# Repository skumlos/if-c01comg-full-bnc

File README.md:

IF-C01COMG Full BNC Clone board SMD

This is a full sized version of the IF-C01COMG board for JVC pro monitors (TM-Hxx50CG) and some others...

It is created as a very close to 1:1 copy of the original (sans the stereo-to-mono mixing circuit and internal 75R term option)
thus it has dual stack BNCs, which are pretty expensive, to allow for passthrough of video signals.

Board is for now completely untested...

You're welcome to clone, sell, re-design and whatever, see LICENSE.

(2022) Martin Hejnfelt (martin@hejnfelt.com)
This work is free. You can redistribute it and/or modify it under the
terms of the Do What The Fuck You Want To Public License, Version 2,
as published by Sam Hocevar. See the LICENSE file for more details.

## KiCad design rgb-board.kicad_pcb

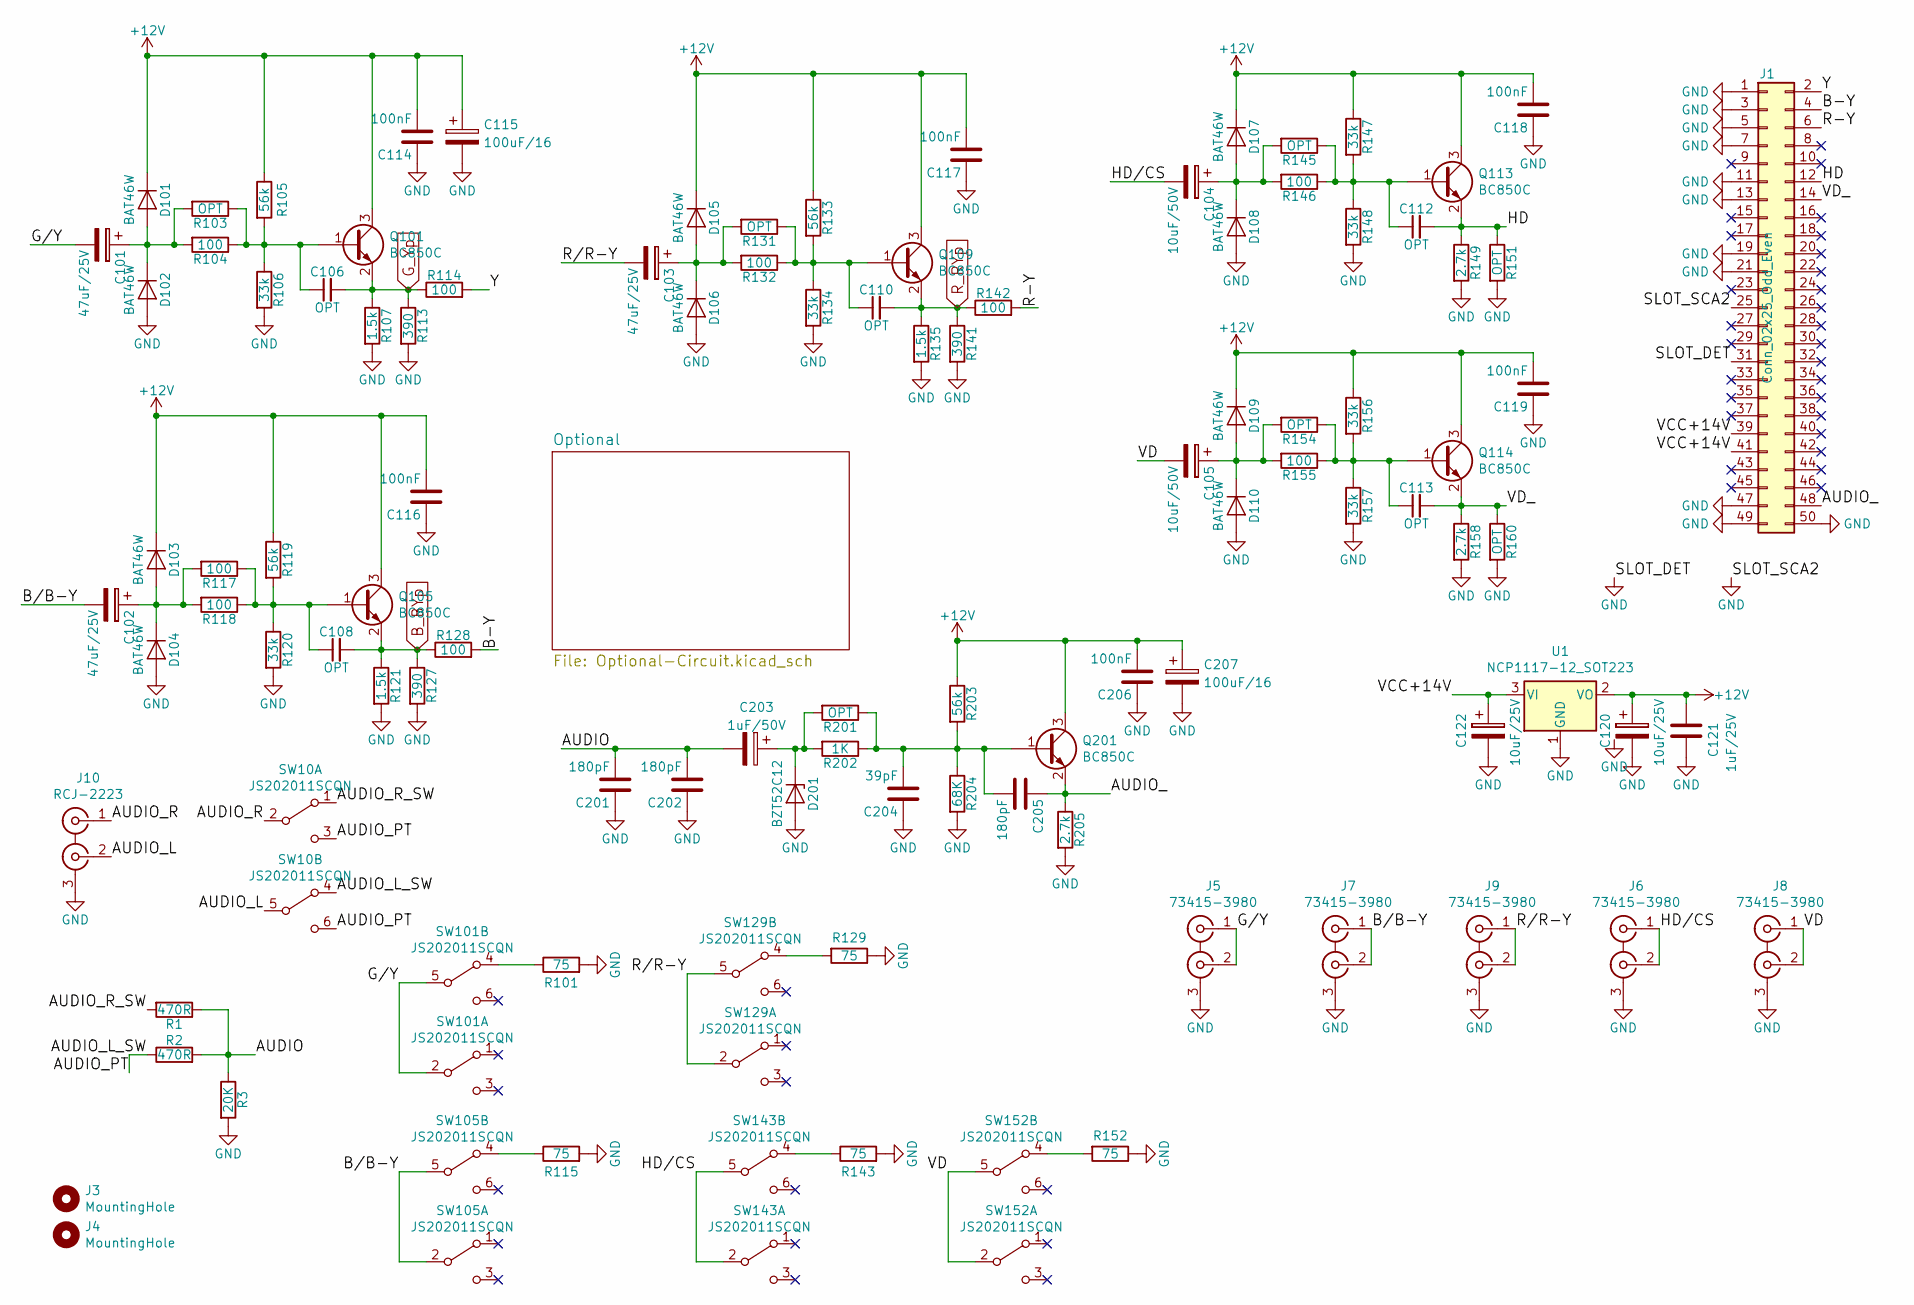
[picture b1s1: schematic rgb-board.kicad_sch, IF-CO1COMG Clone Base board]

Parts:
C101, C102, C103: 47uF/25V; C_Elec_6.3x5.4; JLC SMD,6.3x6.1mm
C104, C105: 10uF/50V; C_Elec_5x5.4; JLC SMD,5x5.4mm
C106, C108, C110, C112, C113: OPT; C_0805_2012Metric_Pad1.18x1.45mm_HandSolder
C114, C116, C117, C118, C119, C206: 100nF; C_0805_2012Metric_Pad1.18x1.45mm_HandSolder; JLC 0805
C115, C207: 100uF/16; CP_Elec_6.3x5.4; JLC SMD,6.3x5.4mm
C120, C122: 10uF/25V; C_Elec_5x5.4; JLC SMD,5x5.4mm
C121: 1uF/25V; C_0805_2012Metric_Pad1.18x1.45mm_HandSolder; JLC 0805
C201, C202, C205: 180pF; C_0805_2012Metric_Pad1.18x1.45mm_HandSolder; JLC 0805
C203: 1uF/50V; CP_Elec_4x5.4; JLC SMD,4x5.4mm
C204: 39pF; C_0805_2012Metric_Pad1.18x1.45mm_HandSolder; JLC 0805
D101, D102, D103, D104, D105, D106, D107, D108, D109, D110: BAT46W; D_SOD-123; JLC SOD-123
D201: BZT52C12; D_SOD-123; JLC SOD-123
J1: Conn_02x25_Odd_Even; Pin_Header_Angled_2x25_Pitch2.54mm
J3, J4: MountingHole; MountingHole_3.2mm_M3
J5, J6, J7, J8, J9: 73415-3980
J10: RCJ-2223; RCJ-22XX
Q101, Q105, Q109, Q113, Q114, Q201: BC850C; SOT-23_Handsoldering; JLC SOT-23(SOT-23-3)
R1, R2: 470R; R_0805_2012Metric_Pad1.20x1.40mm_HandSolder; JLC 0805
R3: 20K; R_0805_2012Metric_Pad1.20x1.40mm_HandSolder; JLC 0805
R101, R115, R129, R143, R152: 75; R_0805_2012Metric_Pad1.20x1.40mm_HandSolder; JLC 0805
R103, R131, R145, R151, R154, R160, R201: OPT; R_0805_2012Metric_Pad1.20x1.40mm_HandSolder; JLC 0805
R104, R114, R117, R118, R128, R132, R142, R146, R155: 100; R_0805_2012Metric_Pad1.20x1.40mm_HandSolder; JLC 0805
R105, R119, R133, R203: 56k; R_0805_2012Metric_Pad1.20x1.40mm_HandSolder; JLC 0805
R106, R120, R134, R147, R148, R156, R157: 33k; R_0805_2012Metric_Pad1.20x1.40mm_HandSolder; JLC 0805
R107, R121, R135: 1.5k; R_0805_2012Metric_Pad1.20x1.40mm_HandSolder; JLC 0805
R113, R127, R141: 390; R_0805_2012Metric_Pad1.20x1.40mm_HandSolder; JLC 0805
R149, R158, R205: 2.7k; R_0805_2012Metric_Pad1.20x1.40mm_HandSolder; JLC 0805
R202: 1K; R_0805_2012Metric_Pad1.20x1.40mm_HandSolder; JLC 0805
R204: 68K; R_0805_2012Metric_Pad1.20x1.40mm_HandSolder; JLC 0805
SW10, SW101, SW105, SW129, SW143, SW152: JS202011SCQN; JLC SMD
U1: NCP1117-12_SOT223; SOT-223-3_TabPin2

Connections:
+12V: C114.2, C115.1, C116.2, C117.2, C118.2, C119.2, C120.1, C121.2, C206.2, C207.1, D101.1 (K), D103.1 (K), D105.1 (K), D107.1 (K), D109.1 (K), Q101.3 (C), Q105.3 (C), Q109.3 (C), Q113.3 (C), Q114.3 (C), Q201.3 (C), R105.1, R119.1, R133.1, R147.1, R156.1, R203.1, U1.2 (VO); also elsewhere on the board
/AUDIO: C201.2, C202.2, C203.2, R1.1, R2.2, R3.1
/AUDIO_: C205.1, J1.48, Q201.2 (E), R205.1
/AUDIO_L: J10.2 (IN2), SW10.5 (B)
/AUDIO_L_SW: R2.1, SW10.3 (C), SW10.4 (A), SW10.6 (C)
/AUDIO_R: J10.1 (IN1), SW10.2 (B)
/AUDIO_R_SW: R1.2, SW10.1 (A)
/B-Y: J1.4, R128.2
/B/B-Y: C102.2, J7.1 (IN1), J7.2 (IN2), SW105.2 (B), SW105.5 (B)
/G/Y: C101.2, J5.1 (IN1), J5.2 (IN2), SW101.2 (B), SW101.5 (B)
/HD: C112.2, J1.12, Q113.2 (E), R149.1, R151.1
/HD/CS: C104.2, J6.1 (IN1), J6.2 (IN2), SW143.2 (B), SW143.5 (B)
/R-Y: J1.6, R142.2
/R/R-Y: C103.2, J9.1 (IN1), J9.2 (IN2), SW129.2 (B), SW129.5 (B)
/VCC+14V: C122.1, J1.39, J1.41, U1.3 (VI)
/VD: C105.2, J8.1 (IN1), J8.2 (IN2), SW152.2 (B), SW152.5 (B)
/VD_: C113.2, J1.14, Q114.2 (E), R158.1, R160.1
/Y: J1.2, R114.2
B_BYp: C108.2, Q105.2 (E), R121.1, R127.1, R128.1; also elsewhere on the board
GND: C114.1, C115.2, C116.1, C117.1, C118.1, C119.1, C120.2, C121.1, C122.2, C201.1, C202.1, C204.1, C206.1, C207.2, D102.2 (A), D104.2 (A), D106.2 (A), D108.2 (A), D110.2 (A), D201.2 (A), J1.1, J1.3, J1.5, J1.7, J1.11, J1.13, J1.19, J1.21, J1.25, J1.31, J1.47, J1.49, J1.50, J5.3 (EXT), J6.3 (EXT), J7.3 (EXT), J8.3 (EXT), J9.3 (EXT), J10.3 (EXT), R3.2, R101.2, R106.2, R107.2, R113.2, R115.2, R120.2, R121.2, R127.2, R129.1, R134.2, R135.2, R141.2, R143.2, R148.2, R149.2, R151.2, R152.1, R157.2, R158.2, R160.2, R204.2, R205.2, U1.1 (GND); also elsewhere on the board
G_Yp: C106.2, Q101.2 (E), R107.1, R113.1, R114.1; also elsewhere on the board
unnamed: C101.1, D101.2 (A), D102.1 (K), R103.2, R104.2
unnamed: C102.1, D103.2 (A), D104.1 (K), R117.2, R118.2
unnamed: C103.1, D105.2 (A), D106.1 (K), R131.2, R132.2
unnamed: C104.1, D107.2 (A), D108.1 (K), R145.2, R146.2
unnamed: C105.1, D109.2 (A), D110.1 (K), R154.2, R155.2
unnamed: C106.1, Q101.1 (B), R103.1, R104.1, R105.2, R106.1
unnamed: C108.1, Q105.1 (B), R117.1, R118.1, R119.2, R120.1
unnamed: C110.1, Q109.1 (B), R131.1, R132.1, R133.2, R134.1
unnamed: C112.1, Q113.1 (B), R145.1, R146.1, R147.2, R148.1
unnamed: C113.1, Q114.1 (B), R154.1, R155.1, R156.2, R157.1
unnamed: C203.1, D201.1 (K), R201.2, R202.2
unnamed: C204.2, C205.2, Q201.1 (B), R201.1, R202.1, R203.2, R204.1
unnamed: R101.1, SW101.4 (A)
unnamed: R115.1, SW105.4 (A)
unnamed: R129.2, SW129.4 (A)
unnamed: R143.1, SW143.4 (A)
unnamed: R152.2, SW152.4 (A)
R_RYp: C110.2, Q109.2 (E), R135.1, R141.1, R142.1; also elsewhere on the board

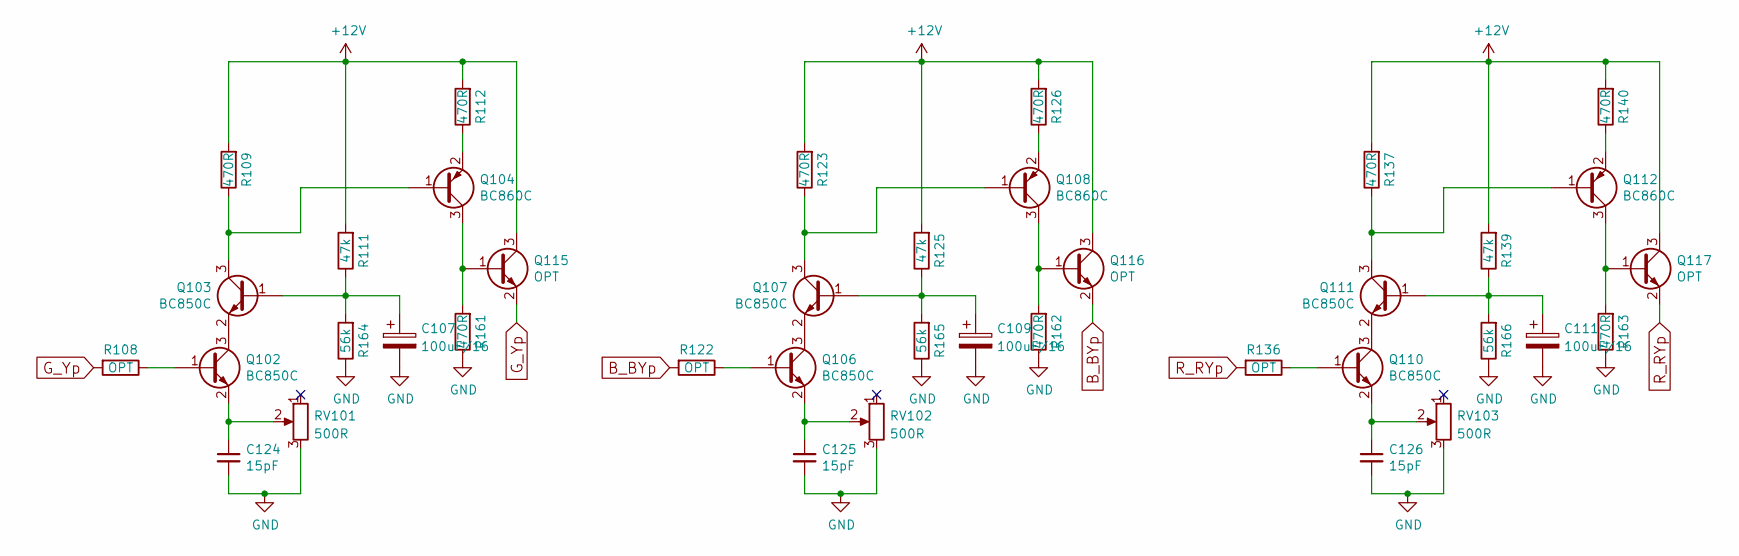
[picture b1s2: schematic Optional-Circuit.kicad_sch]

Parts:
C107, C109, C111: 100uF/16; CP_Elec_6.3x5.4; JLC SMD,6.3x5.4mm
C124, C125, C126: 15pF; C_0805_2012Metric_Pad1.18x1.45mm_HandSolder; JLC 0805
Q102, Q103, Q106, Q107, Q110, Q111: BC850C; SOT-23_Handsoldering; JLC SOT-23(SOT-23-3)
Q104, Q108, Q112: BC860C; SOT-23_Handsoldering; JLC SOT-23
Q115, Q116, Q117: OPT; SOT-23_Handsoldering
R108, R122, R136: OPT; R_0805_2012Metric_Pad1.20x1.40mm_HandSolder
R109, R112, R123, R126, R137, R140, R161, R162, R163: 470R; R_0805_2012Metric_Pad1.20x1.40mm_HandSolder; JLC 0805
R111, R125, R139: 47k; R_0805_2012Metric_Pad1.20x1.40mm_HandSolder; JLC 0805
R164, R165, R166: 56k; R_0805_2012Metric_Pad1.20x1.40mm_HandSolder; JLC 0805
RV101, RV102, RV103: 500R; Potentiometer_Bourns_3386P_Vertical

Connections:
+12V: Q115.3 (C), Q116.3 (C), Q117.3 (C), R109.2, R111.2, R112.2, R123.2, R125.2, R126.2, R137.2, R139.2, R140.2; also elsewhere on the board
B_BYp: Q116.2 (E), R122.2; also elsewhere on the board
GND: C107.2, C109.2, C111.2, C124.2, C125.2, C126.2, R161.1, R162.1, R163.1, R164.1, R165.1, R166.1, RV101.3, RV102.3, RV103.3; also elsewhere on the board
G_Yp: Q115.2 (E), R108.2; also elsewhere on the board
unnamed: C107.1, Q103.1 (B), R111.1, R164.2
unnamed: C109.1, Q107.1 (B), R125.1, R165.2
unnamed: C111.1, Q111.1 (B), R139.1, R166.2
unnamed: C124.1, Q102.2 (E), RV101.2
unnamed: C125.1, Q106.2 (E), RV102.2
unnamed: C126.1, Q110.2 (E), RV103.2
unnamed: Q102.1 (B), R108.1
unnamed: Q102.3 (C), Q103.2 (E)
unnamed: Q103.3 (C), Q104.1 (B), R109.1
unnamed: Q104.2 (E), R112.1
unnamed: Q104.3 (C), Q115.1 (B), R161.2
unnamed: Q106.1 (B), R122.1
unnamed: Q106.3 (C), Q107.2 (E)
unnamed: Q107.3 (C), Q108.1 (B), R123.1
unnamed: Q108.2 (E), R126.1
unnamed: Q108.3 (C), Q116.1 (B), R162.2
unnamed: Q110.1 (B), R136.1
unnamed: Q110.3 (C), Q111.2 (E)
unnamed: Q111.3 (C), Q112.1 (B), R137.1
unnamed: Q112.2 (E), R140.1
unnamed: Q112.3 (C), Q117.1 (B), R163.2
R_RYp: Q117.2 (E), R136.2; also elsewhere on the board

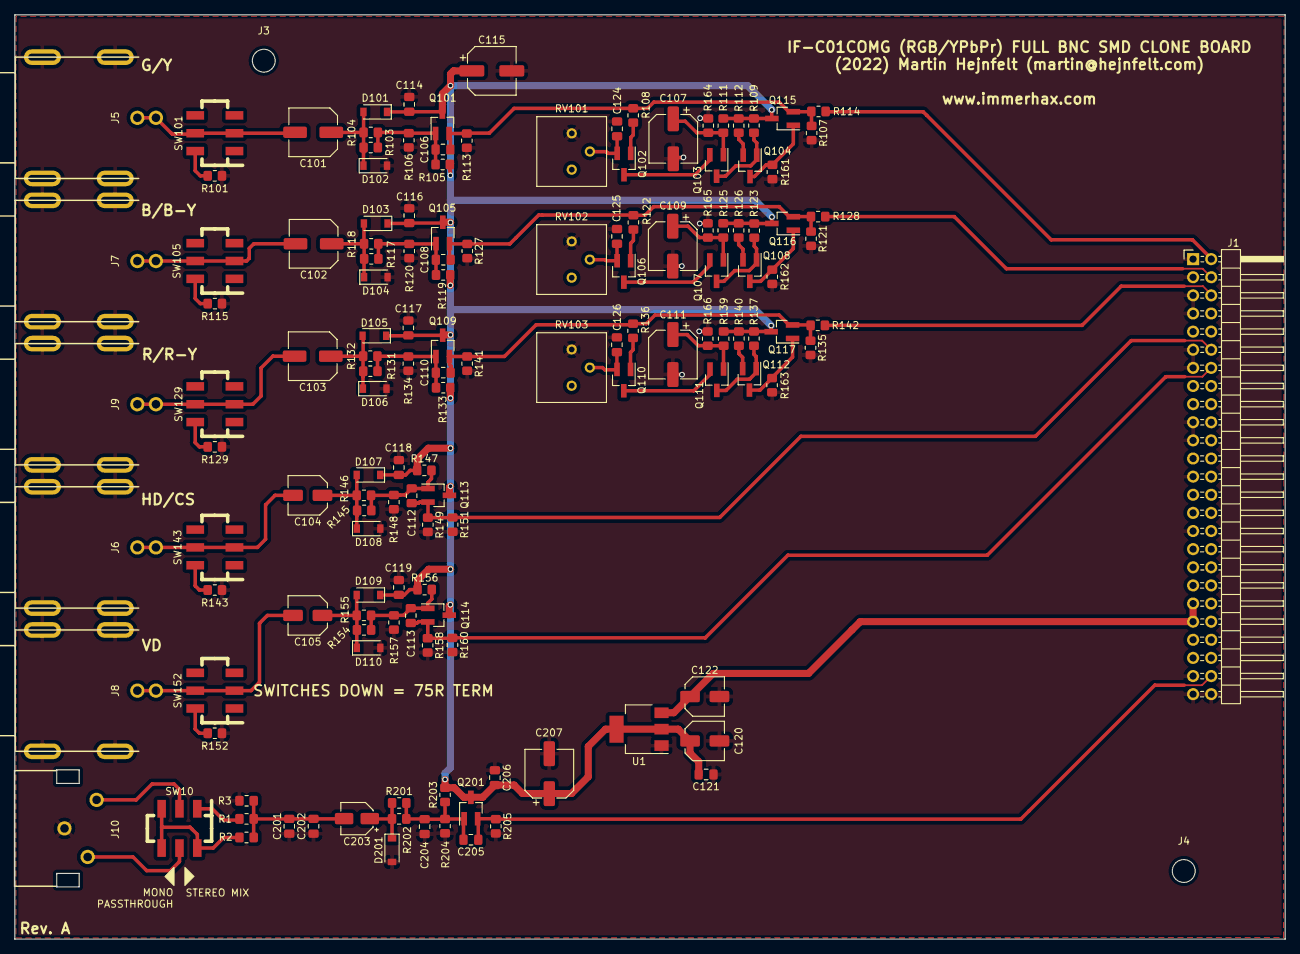
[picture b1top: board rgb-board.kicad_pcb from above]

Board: 2 copper layers, 178.0 x 129.5 mm, 144 parts (0 on the bottom side), 60 nets.

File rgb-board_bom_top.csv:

"Comment","Designator","Footprint","LCSC Part #"
"47uF/25V","C101 C102 C103","SMD,6.3x6.1mm	","C88810"
"10uF/50V","C104 C105","SMD,5x5.4mm","C445070"
"OPT","C106 C108 C110 C112 C113","",""
"100nF","C114 C116 C117 C118 C119 C206","0805","C1711"
"100uF/16","C115 C207 C107 C109 C111","SMD,6.3x5.4mm","C442615"
"10uF/25V","C120 C122","SMD,5x5.4mm	","C445070"
"1uF/25V","C121","0805","C28323"
"180pF","C201 C202 C205","0805","C113826"
"1uF/50V","C203","SMD,4x5.4mm","C445065"
"39pF","C204","0805","C527185"
"BAT46W","D101 D102 D103 D104 D105 D106 D107 D108 D109 D110","SOD-123","C83152"
"BZT52C12","D201","SOD-123","C177013"
"Conn_02x25_Odd_Even","J1","",""
"MountingHole","J3 J4","",""
"73415-3980","J5 J6 J7 J8 J9","",""
"RCJ-2223","J10","",""
"BC850C","Q101 Q105 Q109 Q113 Q114 Q201 Q102 Q103 Q106 Q107 Q110 Q111","SOT-23(SOT-23-3)","C78484"
"470R","R1 R2 R109 R112 R123 R126 R137 R140 R161 R162 R163","0805","C114564"
"20K","R3","0805","C114566"
"75","R101 R115 R129 R143 R152","0805","C141697"
"OPT","R103 R131 R145 R154","0805","C105577"
"100","R104 R114 R117 R118 R128 R132 R142 R146 R155","0805","C105577"
"56k","R105 R119 R133 R203 R164 R165 R166","0805","C137509"
"33k","R106 R120 R134 R147 R148 R156 R157","0805","C141696"
"1.5k","R107 R121 R135","0805","C114555"
"390","R113 R127 R141","0805","C114543"
"2.7k","R149 R158 R205","0805","C144567"
"OPT","R151 R160","0805","C144567"
"OPT","R201","0805","C95781"
"1K","R202","0805","C95781"
"68K","R204","0805","C228958"
"JS202011SCQN","SW10 SW101 SW105 SW129 SW143 SW152","SMD","C221666"
"NCP1117-12_SOT223","U1","",""
"15pF","C124 C125 C126","0805",""
"BC860C","Q104 Q108 Q112","SOT-23","C454976"
"OPT","Q115 Q116 Q117","",""
"OPT","R108 R122 R136","",""
"47k","R111 R125 R139","0805","C126351"
"500R","RV101 RV102 RV103","",""

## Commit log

2022-07-25 Add optional segments, update to Kicad 6
2022-09-15 Update PCB, and plots
